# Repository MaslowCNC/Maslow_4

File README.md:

# Maslow Readme for machines version 4 and 4.1 Current through 2025
## Quicklinks:
Website where you can buy a kit and current assembly instrucitons:
<https://www.maslowcnc.com/>

📚 **Documentation Site (GitHub Pages):**
<https://maslowcnc.github.io/Maslow_4/>

📋 **Changelog (What's New):**
[CHANGELOG.md](./CHANGELOG.md) | [Release Notes v1.16](./docs/ReleaseNotes_v1.16.md) | [Release Notes v1.15](./docs/ReleaseNotes_v1.15.md)

Assembly instructions in wiki:
<https://github.com/MaslowCNC/Maslow_4/tree/assembling-the-arms-4-1>

Repository and wiki:
<https://github.com/MaslowCNC/Maslow_4/wiki>

Forums:
<https://forums.maslowcnc.com/>

How to edit this wiki:
<https://github.com/MaslowCNC/Maslow_4/blob/Maslow-Main/docs/HowToEditThisWiki.md>

This is a rough draft. For more info go to <https://www.maslowcnc.com>

# INTRO

## What is it? 
Maslow is a DIY 3 axis (x,y,z) computer numerical control (CNC) robot that controls a router to cut wood, plastic or other flat material.  It has been designed to work well on a 4x8 foot sheet of material or smaller and it is able to sculpt and cut vertically about 60 mm or 2.5 inches deep.  Maslow is designed around a small sled that carries the router and is anchored to an external frame by long belts that it uses to pull itself around.  This means that the core robot is very portable. It does require a stiff frame or anchors external to the robot.  It rides on top of the work being cut so it works well on cutting and sculpting shallow shapes but not giant bathtub sized hollows. Maslow is focused on accessiblility. 

Maslow's control software is a local website hosted inside the machine that you can access through USBC cable, Wifi direct to the machine, or through your local wifi network. It can be used with a phone or a computer. It recieves standard Gcode machine instruction files (.nc)  You will need cnc design software that can generate Gcode. There are many free or fancy options. 

The control software is built on top of FluidNC an open source cnc control software for ESP32 computers. Maslow4's pcb is an esp32 computer.

The FluidNC project wiki is here: 

<http://wiki.fluidnc.com/>

Github:

<https://github.com/bdring/FluidNC>

Donate to FluidNC:

Maslow4 is different from a gantry designed CNC router which are designed around a table that fits the material inside and then the robot moves forward and back on rails. It is much much less expensive than a gantry machine. It is in general less accurate than a good gantry machine. Gantry machines can also be 4 or 5 axis machines in which they can rotate the material in order to cut it at different angles. 

Maslow is a project developed by Barbour Smith and a community of volunteers and forum members as an open source project that is still under development.  It is portable, exciting, inexpensive and perhaps frustrating and still requires some troubleshooting and figuring out to get started.  Barbour has been working on iterations of this for more than a decade and many people have been successful at making many exciting projects including saunas, tables, signs, and a 30 foot catamaran! (link to project gallery) but it is not at the moment a perfect plug and play tool.  **If making your own portable blade wielding robot in an enthusiastic online community sounds fun, then you are probably in the right place.** 

# History (I don't know a lot here) 
 In ???? Barbour Smith designed the first Maslow as a wall mounted CNC routing robot that hung from two chains and pulled itself back and forth across a space. The robot at that point was designed around an Arduino Mega 2560 microcontroller and was an open source design. Barbour set up the forums and github groups and sold ??? machines. 

 It is still possible to make a Maslow Version 1, 2, or 3 and many people have been happy with them as useful tools. Makermade was a company that sold version ?2? under the open source license that is not affiliated directly with Maslow's developers. 

 The current version Maslow 4 was prototyped as 3D printed parts with standard hardware. It has four machine belts instead of two chains. The parts are not interchangable with earlier versions. It uses a custom printed circuit board PCB built around an ESP microcontroller. The board also incorporates motor controllers. 

It is still possible to 3D print your own parts and replacement parts. It is still possible to design and program your own generic ESP microcontroller and use off the shelf motor controllers. In ?2023? Barbour ran a successful Kickstarter campaign with which he used the proceeds to design and have injection molds made for injection molded parts and better compact custom PCBs. Injection molded parts are much stronger than most 3d printed parts. This is what you are buying when you buy a Maslow kit. The custom PCB, the custom wires, the motors and custom made hardware, nuts and bolts, and the injection molded plastics with fiberglass inclusions. 4.1 was the result of a second kickstarter campaign that upgraded the PCB, wire connectors, the nuts and bolts and other metal hardware as well as a better spool design.

# Community members who have made significant contributions:
bar founder and primary developer

dlang ?Programming?

Ian_ab?Programming? 

# How to get involved
Maslow is a truly open source project. The forums are active with helpers and anybody can add to the discussions there or add to the project here in the github repo.  You can't mess things up here as final commits have to be checked.
The creative community needs to share fun projects, fun adapatations of the robot and support frames, hacks and troubleshooting tips, programming fixes, and documentation. 

/Firmware is edited and developed by volunteers, you can try too, the Github Maslow AI can be asked to change the programming. 

Three D Printing files and parts lists will soon be in the repo for downloading and editing or adapting

/docs holds documentation and instructions.  If you have a good idea to make things more clear or help other people understand the machine you could add something there

To edit a file here navigate to the file you want to edit, open it, then click on the little pencil in the top corner and it will open an editing window. When you are editing you are making a temporary branch of the main repo. This branch is a copy of the main repo that can be compared and if useful written back into the main repo. The human readable document pages are written in markdown language, a kind of simple word processor. Markdown instructions are in a link at the bottom of the editing window.  Once you have edited the document you can commit changes and then make a pull request asking for it to be written back to the main branch.  

# Future of the project
Currently the focus is on making the Maslow4 run quickly and easily mostly through firmware development. Community members are playing with different 3d printed adaptations of the main parts as well as both larger and smaller frames. The goal would be to keep developing the software now and then have an updated hardware kit in several years. A sister project to Maslow is Abundance, which is working towards being an open source web browser based parametric cad system that could feed directly to Maslow <https://abundance.maslowcnc.com/>
(written 2025) 

# Safety and hazards
Power tools are inherently powerful and can be dangerous.  This is an open source project created and maintained by amatuer enthusiasts with designs that have not been tested or evaluated for safety. Follow any instructions here at your own risk and using your own judgement.  The authors of this project make no claims about the saftey or suitability of the designs, ideas, or instructions. Any safety advice is provided in good faith. Use and modify the information in this project at your own risk. 

Below is a list of common sense hazards for you to consider

## Hazards may include:
- **Electrical shock or fire** if used in a damp or wet area or if electrical insulation or protective covering is damaged or removed. Always check your wires, connections and PCB cover for damage. Make sure airflow to the machine is not blocked or restricted. Different routers and spindles will require different airflow. Do not leave the machine unattended while it is in use. Have a plan to cut power to the machine in an emergency. 
- **Dust inhalation and dust fire**. Routers create dust and heat as blades cut through material.  Evaluate the material you are cutting and take dust mitigation measures including working in the open air, using dust vacuum systems, dust masks and appropriate respirators.
- **Friction fire hazard.** Blades create heat through friction, this can cause material being cut or other nearby items to ignite, smoke, or smolder. This is especialy dangerous when a power tool gets stuck in one place or bound up in the material being cut. While the machine is running do not leave it unattended and test and evaluate the material being cut and the feed rate, moving speed, and rotational speed for suitablility for each job. Materials may produce fumes while being cut. 
- **Laceration, burns, pinching, and crushing**. Never touch the blade of a router without saftey measures. Router bits are very sharp and will be hot after use. The motors and belts can entangle hair or loose clothing and fingers or other body parts could be pinched or torn while the machine is moving. Care has been taken in the design to minimize these risks.  Keep clear of the the machine while motors are engaged. Make sure both the router and the control board are unplugged and off before changing bits or touching the machine.
- **Eye, skin, or equipment damage from backlash or flying debris**.  Spinning power tool blades can throw pieces of themselves or cut material at great speed. Robotic motors put belts and parts under strain which can result in breakage and pieces being thrown with speed. Wear eye protection at all times when the machine is running and only use the machine in a controlled environment where bystanders are protected from flying debris. Do not leave the machine unattended.
- **Hearing Damage**. Routers and robots can easily exceed safe noise thresholds while running. Wear appropriate hearing proection while the machine is in use.

## Overall saftey meaures
- Regularly check your machine  for evidence of wear or damage.
- Only use in a safe and controlled space. 
- Do not leave the machine running unattended.
- Use personal protective equipment including masks, respirators, gloves, hearing protection,  and eye protection. 
- Do not touch the machine while it is moving or turned on.
- Do not change blades while the machine is plugged in. 
- Have a fire suppression plan and equipment.
- Consider how you will cut power to the machine in an emergency.
- Check for loose parts, tools, keys, and if the blades are in an appropriate place before providing power to the machine. 
- Train yourself and anyone who will come in contact with the machine on your saftely plan. 

CNC routers are nice in that they may be operated at a greater distance than a handheld router.  Many of the vibration, inhalation, and flying debris dangers are less with a robotic controler.  CNC machines are dangerous when people leave them unattended and beacause there are more motors, more electrical connections, and more moving parts.

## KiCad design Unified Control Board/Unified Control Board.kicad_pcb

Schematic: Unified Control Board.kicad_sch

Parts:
C1, C7, C10, C18: 22uF; CAP-SMD_BD6.3-L6.6-W6.6-LS7.3-FD; MPN RT1J220M0607
C5, C9, C16, C160, C161, C162, C163: 100nF/100V; C0603; MPN CL10B104KC8NNNC
C8, C11, C19, C20, C26: 1uF; C0402; MPN CL05A105KA5NQNC
C21: 22uF; C0805; MPN CL21A226MAQNNNE
C22: 100nF; C0603; MPN CC0603KRX7R9BB104
C23: 10uF; C0805; MPN CL21A106KAYNNNE
C24, C25: 22pF; C0603; MPN CC0603JRNPO9BN220
C27, C74, C75: 330uF/50V; CAP-SMD_BD10.0-L10.3-W10.3-LS10.9-FD; MPN EEEFT1H331AP
C28: 220uF/50V; CAP-SMD_BD10.0-L10.3-W10.3-LS10.9-FD; MPN UCD1H221MNL1GS
C29: 12nF; C0402; MPN CC0402KRX7R9BB123; LCSC Part Name 1nF ±10% 50V X7R 0402 MLCC
C30: 82pF; C0402; MPN CC0402JRNPO9BN820; LCSC Part Name 1nF ±10% 50V X7R 0402 MLCC
C31: 100nF; C0603; MPN CC0603KRX7R9BB104; LCSC Part Name 1nF ±10% 50V X7R 0402 MLCC
C32: 10uF; C0805; MPN GRM21BR61H106KE43L; LCSC Part Name 10uF ±10% 50V
C33: 22uF; C0805; MPN CL21A226MAQNNNE; LCSC Part Name 10uF ±10% 50V
C34, C36, C42, C49, C54, C61: 100nF; C0603; MPN CC0603KRX7R9BB104; LCSC Part Name 100nF ±10% 50V
C39, C60: 100uF/50V; CAP-TH_BD8.0-P3.50-D0.6-FD; MPN 50YXF100MEFC8X11.5; LCSC Part Name 100uF ±20% 50V (alt: Chengx KM107M050F1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
C40, C44: 1uF; C0402; MPN CL05A105KA5NQNC; LCSC Part Name 1uF ±10% 25V
C56: 22uF; C0805; MPN CL21A226MAQNNNE; LCSC Part Name 22µF ±20% 16V X5R 0805 MLCC
C63: 22uF; C0805; MPN CL21A226MAQNNNE; LCSC Part Name 22uF ±20% 16V X5R 0805 MLCC
C72: 10uF/25V; C0805; MPN CL21A106KAYNNNE
C73: 220nF/100V; C0805; MPN CC0805KKX7R0BB224
CGQ1: IR12-21C/TR8; LED-SMD_IR12-21C-TR8; MPN IR12-21C/TR8; LCSC Part Name 65mA红外发射管
CN1, CN2, CN3, CN6: B02B-PASK(LF)(SN); CONN-TH_B02B-PASK; MPN B02B-PASK(LF)(SN)
CN4, CN5, CN7, CN8: B04B-PASK(LF)(SN); CONN-TH_B04B-PASK; MPN B04B-PASK(LF)(SN)
CN9, CN10, CN11: B3B-XH-2(LF)(SN); CONN-TH_B3B-XH-2-LF-SN; MPN B3B-XH-2(LF)(SN); LCSC Part Name 1x3P 间距:2.5mm 直插 系列:XH
D1, D2, D5: RB050L-60TE25; SMA_L4.2-W2.6-LS5.3-RD; MPN RB050L-60TE25
D3: SMCJ36A; SMC_L7.1-W6.2-LS8.1-R-RD; MPN SMCJ36A; LCSC Part Name SMCJ36A
D6: BZT52C15; D_SOD-123; MPN BZT52C15
H1, H2: SMTSOM330BTR; SMTSO-M3_SMD-Ring_Hole4.22; MPN SMTSOM330BTR
IR1: PT12-21C/TR8; SENSOR-SMD_L3.0-W2.0-RD; MPN PT12-21C/TR8; LCSC Part Name 940nm的NPN光电三极管
L1: 4.7uH; L_APV_ANR4030; MPN FNR4030S4R7MT
LED1: LED-0603_R; LED0603_RED; MPN KT-0603R
LED2: FC-DA1608BK-470H10; LED0603-RD; MPN NCD0603B1
LED3: green; LED0603-RD-YELLOW; MPN KT-0603YG; LCSC Part Name Green 570nm 0603 LED, Vf 2.0-2.2V, 30-4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
Q1: ME50P06-G; TO-252-2; MPN ME50P06-G
R1, R11, R12, R21: 680Ω; R0402; MPN 0402WGF6800TCE
R2, R3: 120Ω; R0603; MPN 0603WAF1200T5E
R4: 2.2kΩ; R0402; MPN 0402WGF2201TCE
R5, R7, R14, R15, R16, R17, R18, R22, R23, R24: 1kΩ; R0402; MPN 0402WGF1001TCE
R8, R13: 5.1kΩ; R0402; MPN 0402WGF5101TCE
R9, R10, R19, R20, R25, R26, R28: 10kΩ; R0402; MPN 0402WGF1002TCE
R27: 62kΩ; R0402; MPN 0402WGF6202TCE; LCSC Part Name 3.3kΩ ±1% 1/16W 0402 Chip Resistor
R29: 20kΩ; R0402; MPN 0402WGF2002TCE; LCSC Part Name 3.3kΩ ±1% 1/16W 0402 Chip Resistor
R30: 200kΩ; R0402; MPN 0402WGF2003TCE; LCSC Part Name 3.3kΩ ±1% 1/16W 0402 Chip Resistor
R31: 7.5kΩ; R0402; MPN 0402WGF7501TCE; LCSC Part Name 7.5kΩ ±1% 1/16W 0402 Chip Resistor
R38, R39, R45: 10kΩ; R0402; MPN 0402WGF1002TCE; LCSC Part Name 10kΩ ±1% 62.5mW 厚膜电阻
R44: 100Ω; R0402; MPN 0402WGF1000TCE; LCSC Part Name 100Ω ±1% 1/16W 0402 Chip Resistor
R58: 330Ω; R0402; MPN 0402WGF3300TCE; LCSC Part Name 330Ω ±1% 1/16W 0402 Chip Resistor
R59: 47kΩ; R0402; MPN 0402WGF4702TCE
R60: 100kΩ; R0402; MPN 0402WGF1003TCE
SW1, SW2, SW3: TSA002A3512A02; SW-SMD_BZCN_TSA002A35XXX; MPN TSA002A3512A02; LCSC Part Name 4.8*2*3.5mm 卧贴 轻触开关
U1: XT60PB-M.G.Y; CONN-TH_XT60PB-M; MPN XT60PB-M.G.Y
U2, U3, U4, U5: DRV8251ADDAR; SOIC-8-1EP_DDA0008B_ThermalVias_0.3mm; MPN DRV8251ADDAR
U6: TCA9546A; SOP-16_L5.0-W4.4-P0.65-LS6.4-BL; MPN TCA9546APWR,118
U7: ZDSD01GLGEAG; LGA-8_L6.0-W8.0-P1.27-BL; MPN ZDSD01GLGEAG
U8: ESP32-S3-WROOM-1; MPN ESP32-S3-WROOM-1
U9: TPS54360BDDAR; AP64350SP_SO-8-EP; MPN TPS54360BDDAR
USB1: KH-TYPE-C-16P; USB-C-SMD_KH-TYPE-C-16P; MPN KH-TYPE-C-16P

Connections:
3V3: C21.1, C22.2, C23.2, C33.1, C40.2, C42.2, C44.2, C49.2, C54.2, C56.1, C61.2, C63.2, CN4.4, CN5.4, CN7.4, CN8.4, L1.2, R5.2, R7.2, R14.2, R15.2, R16.2, R17.2, R18.2, R22.2, R23.1, R24.2, R25.2, R26.2, R27.1, R28.2, R38.2, R45.2, R58.2, SW3.2, U2.4 (VREF), U3.4 (VREF), U4.4 (VREF), U5.4 (VREF), U6.3 (/RESET), U6.16 (VDD), U7.8 (Vdd,power_supply), U8.2 (VDD33); also elsewhere on the board
/YLED: LED3.2 (A), R58.1
ADC BL: C20.2, R20.1, U8.12 (IO8)
ADC BR: C8.2, R9.1, U8.7 (IO7)
ADC TL: C19.2, R19.1, U8.11 (IO18)
ADC TR: C11.2, R10.1, U8.6 (IO6)
Axis Health LED: R3.2, U8.22 (IO14)
BEAMBREAK: IR1.1 (C), R45.1; also elsewhere on the board
BL IN1: U5.3 (IN1), U8.30 (IO37)
BL IN2: U5.2 (IN2), U8.29 (IO36)
BL OUT1: CN1.2, U5.6 (OUT1)
BL OUT2: CN1.1, U5.8 (OUT2)
BR IN1: U2.3 (IN1), U8.17 (IO9)
BR IN2: U2.2 (IN2), U8.15 (IO3)
BR OUT1: CN2.2, U2.6 (OUT1)
BR OUT2: CN2.1, U2.8 (OUT2)
BST: C31.1, U9.1 (BST)
BoardCOM1: U8.9 (IO16); also elsewhere on the board
BoardCOM2: U8.8 (IO15); also elsewhere on the board
BoardVersion: R4.2, R26.1, U8.10 (IO17)
Boot: SW1.1, U8.27 (IO0)
CLKV: U7.3 (CLK,clock_signal), U8.20 (IO12)
COMP: C30.1, R31.1, U9.6 (COMP)
COMP_Z: C29.1, R31.2
DETECTORLED: R44.2; also elsewhere on the board
FAULT: R28.1, U8.33 (IO40)
FB: R27.2, R29.1, U9.5 (FB)
GND: C1.2, C5.1, C7.2, C8.1, C9.1, C10.2, C11.1, C16.1, C18.2, C19.1, C20.1, C21.2, C22.1, C23.1, C24.1, C25.1, C26.1, C27.2, C28.2, C29.2, C30.2, C32.2, C33.2, C34.1, C36.1, C39.2, C40.1, C42.1, C44.1, C49.1, C54.1, C56.2, C60.2, C61.1, C63.1, C74.2, C75.2, C160.1, C161.1, C162.1, C163.1, CGQ1.1 (C), CN4.1, CN5.1, CN7.1, CN8.1, CN10.3, D3.1 (A), D5.2 (A), IR1.2 (E), LED1.2, LED2.1 (-), LED3.1 (C), R1.1, R4.1, R8.1, R11.1, R12.1, R13.1, R21.1, R29.2, R30.2, R39.2, R60.2, SW1.2, SW2.2, U1.2, U2.7 (GND), U2.9 (PAD), U3.7 (GND), U3.9 (PAD), U4.7 (GND), U4.9 (PAD), U5.7 (GND), U5.9 (PAD), U6.1 (A0), U6.2 (A1), U6.8 (VSS), U6.13 (A2), U7.4 (Vss,ground), U8.1 (GND), U8.40 (GND), U8.41 (EPAD), U9.7 (GND), U9.9 (EP), USB1.1 (EP), USB1.2 (EP), USB1.3 (EP), USB1.4 (EP), USB1.A1 (GND), USB1.A12 (GND), USB1.B1 (GND), USB1.B12 (GND); also elsewhere on the board
MCU_RST: C26.2, R25.1, U8.3 (EN)
MISOV: U7.6 (SD0,I/O_pin), U8.21 (IO13)
MOSIV: U7.5 (CMD,command_signal), U8.19 (IO11)
unnamed: CGQ1.2 (A), R44.1
unnamed: LED1.1, R3.1
unnamed: LED2.2 (+), R2.1
unnamed: R9.2, R11.2, U2.1 (IPROPI)
unnamed: R10.2, R12.2, U3.1 (IPROPI)
unnamed: R19.2, R21.2, U4.1 (IPROPI)
unnamed: R1.2, R20.2, U5.1 (IPROPI)
unnamed: R8.2, USB1.A5 (CC1)
unnamed: R13.2, USB1.B5 (CC2)
PHA1: CN9.1; also elsewhere on the board
PHA2: CN11.1; also elsewhere on the board
PHB1: CN9.2; also elsewhere on the board
PHB2: CN11.2; also elsewhere on the board
PHC1: CN9.3; also elsewhere on the board
PHC2: CN11.3; also elsewhere on the board
RT: R30.1, U9.4 (RT/CLK)
SCL: R14.1, U6.14 (SCL), U8.4 (IO4)
SCL0: CN7.2, R22.1, U6.5 (SC0)
SCL1: CN4.2, R23.2, U6.7 (SC1)
SCL2: CN8.2, R17.1, U6.10 (SC2)
SCL3: CN5.2, R15.1, U6.12 (SC3)
SDA: R7.1, U6.15 (SDA), U8.5 (IO5)
SDA0: CN7.3, R5.1, U6.4 (SD0)
SDA1: CN4.3, R24.1, U6.6 (SD1)
SDA2: CN8.3, R18.1, U6.9 (SD2)
SDA3: CN5.3, R16.1, U6.11 (SD3)
SD_CS: U7.2 (SD3,I/O_pin), U8.18 (IO10)
SPINDLE_BOOT0: C36.2, R39.1, SW3.1; also elsewhere on the board
SPINDLE_BOOT_X: U8.38 (IO2); also elsewhere on the board
SPINDLE_NRST: C34.2, R38.1, SW2.1; also elsewhere on the board
SPINDLE_RST_X: U8.39 (IO1); also elsewhere on the board
SS_GATE: C72.2, C73.1, D6.2 (A), Q1.1 (G), R59.2, R60.1
SW_NODE: C31.2, D5.1 (K), L1.1, U9.8 (SW)
TL IN1: U4.3 (IN1), U8.26 (IO45)
TL IN2: U4.2 (IN2), U8.23 (IO21)
TL OUT1: CN6.2, U4.6 (OUT1)
TL OUT2: CN6.1, U4.8 (OUT2)
TR IN1: U3.3 (IN1), U8.35 (IO42)
TR IN2: U3.2 (IN2), U8.34 (IO41)
TR OUT1: CN3.2, U3.6 (OUT1)
TR OUT2: CN3.1, U3.8 (OUT2)
USB5V: D2.2 (A), USB1.A4 (VBUS), USB1.A9 (VBUS), USB1.B4 (VBUS), USB1.B9 (VBUS)
USBD+: C24.2, U8.14 (IO20), USB1.A6 (DP1), USB1.B6 (DP2)
USBD-: C25.2, U8.13 (IO19), USB1.A7 (DN1), USB1.B7 (DN2)
VAC_CONTROL: CN10.1; also elsewhere on the board
VCC: C1.1, C5.2, C7.1, C9.2, C10.1, C16.2, C18.1, C27.1, C39.1, C60.1, C73.2, C74.1, C75.1, C160.2, C161.2, C162.2, C163.2, CN10.2, D1.2 (A), D3.2 (K), Q1.2 (D), U2.5 (VM), U3.5 (VM), U4.5 (VM), U5.5 (VM); also elsewhere on the board
VIN_RAW: C72.1, D6.1 (K), Q1.3 (S), R59.1, U1.1
VSUP: C28.1, C32.1, D1.1 (K), D2.1 (K), U9.2 (VIN)
WiFi LED: R2.2, U8.28 (IO35)

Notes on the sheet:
Motor Drivers
-PMOS gate VBUS pull-up to prevent reverse current to buck output -This provides low voltage drop BUCK starts at 3.3V default -Also prioritizes VBUS over BUCK
ESP32
3.3V Regulator
Beam Break Homing System
Microcontroller
BOOT button
ESP32-S3
Fan Control System
RESET button
Power Led
Integrated MOTOR Driver
200ma LDO / Power OR-ing with PMOS
Power Regulator
This is a low pass filter on the value from the current measuring parts
Type C - Female USB
Decoupling capacitors
Control for the vacuum dust collection system
USB
For Programming & Debugging
PHASE-CURRENT ADC (24V test of the 36V-branch front end) SOx (3.3k/3.3k bias, 1.65V = 0A) -> straight to ADS7038 AIN0-5; no ESP32 copy, no RC at the ADC pin. AIN0-2 = motor 1 A/B/C, AIN3-5 = motor 2 A/B/C, AIN6/AIN7 spare. Ref = AVDD = 3V3 (ratiometric with the bias). SPI on U10: IO37 CS (10k pull-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
M3 MOUNTING: SMD threaded standoffs soldered on the bottom under the two lower mounting holes (4.22 mm unplated hole, 6.6 mm ring, not connected). A bolt from the top threads straight in.

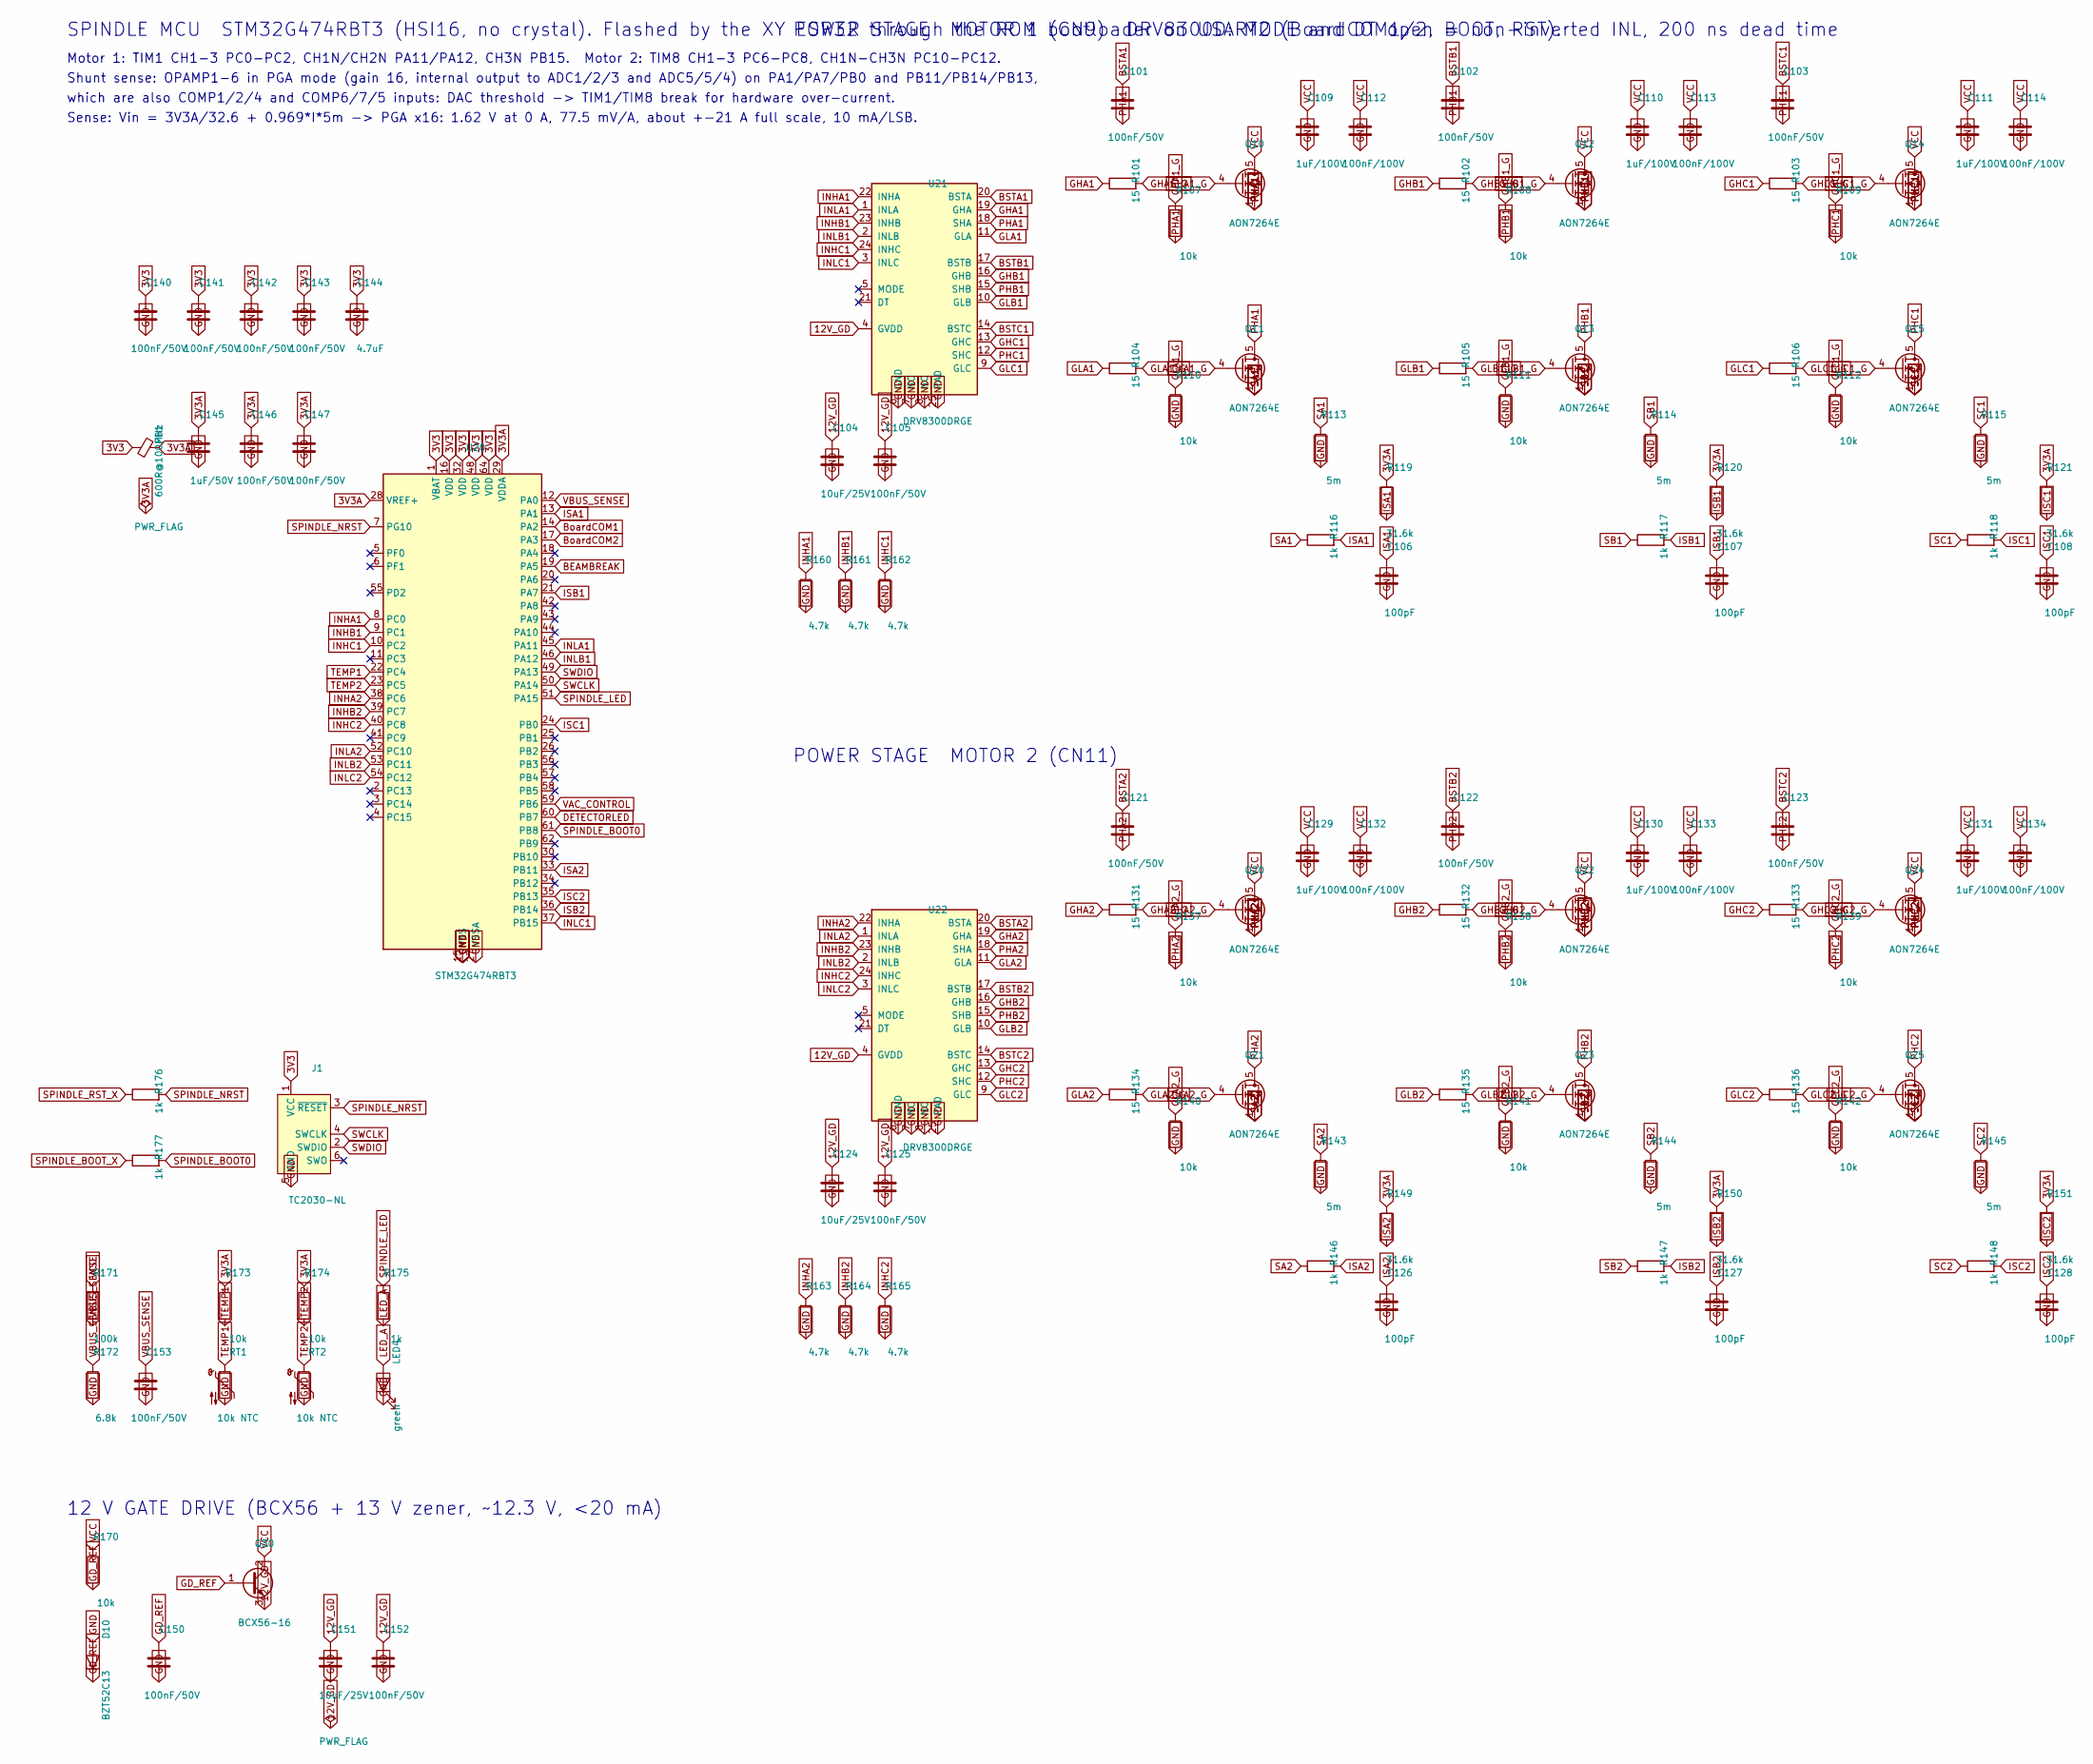
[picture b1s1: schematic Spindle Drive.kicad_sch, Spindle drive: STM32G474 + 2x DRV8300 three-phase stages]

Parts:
C101, C102, C103, C105, C121, C122, C123, C125, C140, C141, C142, C143, C146, C147, C150, C152, C153: 100nF/50V; C_0603_1608Metric; MPN CC0603KRX7R9BB104
C104, C124: 10uF/25V; C_0603_1608Metric; MPN GRM188R61E106MA73D
C106, C107, C108, C126, C127, C128: 100pF; C_0402_1005Metric; MPN 0402CG101J500NT
C109, C110, C111, C129, C130, C131: 1uF/100V; C_1206_3216Metric; MPN CL31B105KCHNNNE
C112, C113, C114, C132, C133, C134: 100nF/100V; C_0603_1608Metric; MPN CL10B104KC8NNNC
C144: 4.7uF; C_0603_1608Metric; MPN CL10A475KO8NNNC
C145: 1uF/50V; C_0603_1608Metric; MPN CL10A105KB8NNNC
C151: 10uF/25V; C_0805_2012Metric; MPN CL21A106KAYNNNE
D10: BZT52C13; D_SOD-123; MPN BZT52C13
FB1: 600R@100MHz; L_0603_1608Metric; MPN GZ1608D601TF
J1: TC2030-NL; Tag-Connect_TC2030-IDC-NL_2x03_P1.27mm_Vertical
LED4: green; LED_0603_1608Metric; MPN 19-213/Y2C-CQ2R2L/3T(CY)
Q10, Q11, Q12, Q13, Q14, Q15, Q20, Q21, Q22, Q23, Q24, Q25: AON7264E; AOS_DFN-8-1EP_3x3mm_P0.65mm; MPN AON7264E
Q30: BCX56-16; SOT-89-3; MPN BCX56-16
R101, R102, R103, R104, R105, R106, R131, R132, R133, R134, R135, R136: 15; R_0402_1005Metric; MPN 0402WGF150JTCE
R107, R108, R109, R110, R111, R112, R137, R138, R139, R140, R141, R142, R173, R174: 10k; R_0402_1005Metric; MPN 0402WGF1002TCE
R113, R114, R115, R143, R144, R145: 5m; R_1206_3216Metric; MPN STE1206M1W0R005FS
R116, R117, R118, R146, R147, R148, R175, R176, R177: 1k; R_0402_1005Metric; MPN 0402WGF1001TCE
R119, R120, R121, R149, R150, R151: 31.6k; R_0402_1005Metric; MPN 0402WGF3162TCE
R160, R161, R162, R163, R164, R165: 4.7k; R_0402_1005Metric; MPN 0402WGF4701TCE
R170: 10k; R_0603_1608Metric; MPN 0603WAF1002T5E
R171: 100k; R_0402_1005Metric; MPN 0402WGF1003TCE
R172: 6.8k; R_0402_1005Metric; MPN 0402WGF6801TCE
RT1, RT2: 10k NTC; R_0603_1608Metric; MPN NCP18XH103F03RB
U20: STM32G474RBT3; LQFP-64_10x10mm_P0.5mm; MPN STM32G474RBT3
U21, U22: DRV8300DRGE; VQFN-24-1EP_4x4mm_P0.5mm_EP2.45x2.45mm; MPN DRV8300DRGER

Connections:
3V3: C140.1, C141.1, C142.1, C143.1, C144.1, FB1.1, J1.1 (VCC), U20.1 (VBAT), U20.16 (VDD), U20.32 (VDD), U20.48 (VDD), U20.64 (VDD); also elsewhere on the board
3V3A: C145.1, C146.1, C147.1, FB1.2, R119.1, R120.1, R121.1, R149.1, R150.1, R151.1, R173.1, R174.1, U20.28 (VREF+), U20.29 (VDDA)
12V_GD: C104.1, C105.1, C124.1, C125.1, C151.1, C152.1, Q30.3 (E), U21.4 (GVDD), U22.4 (GVDD)
BEAMBREAK: U20.19 (PA5); also elsewhere on the board
BSTA1: C101.1, U21.20 (BSTA)
BSTA2: C121.1, U22.20 (BSTA)
BSTB1: C102.1, U21.17 (BSTB)
BSTB2: C122.1, U22.17 (BSTB)
BSTC1: C103.1, U21.14 (BSTC)
BSTC2: C123.1, U22.14 (BSTC)
BoardCOM1: U20.14 (PA2); also elsewhere on the board
BoardCOM2: U20.17 (PA3); also elsewhere on the board
DETECTORLED: U20.60 (PB7); also elsewhere on the board
GD_REF: C150.1, D10.1 (K), Q30.1 (B), R170.2
GHA1: R101.1, U21.19 (GHA)
GHA1_G: Q10.4 (G), R101.2, R107.1
GHA2: R131.1, U22.19 (GHA)
GHA2_G: Q20.4 (G), R131.2, R137.1
GHB1: R102.1, U21.16 (GHB)
GHB1_G: Q12.4 (G), R102.2, R108.1
GHB2: R132.1, U22.16 (GHB)
GHB2_G: Q22.4 (G), R132.2, R138.1
GHC1: R103.1, U21.13 (GHC)
GHC1_G: Q14.4 (G), R103.2, R109.1
GHC2: R133.1, U22.13 (GHC)
GHC2_G: Q24.4 (G), R133.2, R139.1
GLA1: R104.1, U21.11 (GLA)
GLA1_G: Q11.4 (G), R104.2, R110.1
GLA2: R134.1, U22.11 (GLA)
GLA2_G: Q21.4 (G), R134.2, R140.1
GLB1: R105.1, U21.10 (GLB)
GLB1_G: Q13.4 (G), R105.2, R111.1
GLB2: R135.1, U22.10 (GLB)
GLB2_G: Q23.4 (G), R135.2, R141.1
GLC1: R106.1, U21.9 (GLC)
GLC1_G: Q15.4 (G), R106.2, R112.1
GLC2: R136.1, U22.9 (GLC)
GLC2_G: Q25.4 (G), R136.2, R142.1
GND: C104.2, C105.2, C106.2, C107.2, C108.2, C109.2, C110.2, C111.2, C112.2, C113.2, C114.2, C124.2, C125.2, C126.2, C127.2, C128.2, C129.2, C130.2, C131.2, C132.2, C133.2, C134.2, C140.2, C141.2, C142.2, C143.2, C144.2, C145.2, C146.2, C147.2, C150.2, C151.2, C152.2, C153.2, D10.2 (A), J1.5 (GND), LED4.1 (K), R110.2, R111.2, R112.2, R113.2, R114.2, R115.2, R140.2, R141.2, R142.2, R143.2, R144.2, R145.2, R160.2, R161.2, R162.2, R163.2, R164.2, R165.2, R172.2, RT1.2, RT2.2, U20.15 (VSS), U20.27 (VSSA), U20.31 (VSS), U20.47 (VSS), U20.63 (VSS), U21.6 (GND), U21.7 (NC), U21.8 (NC), U21.25 (PAD), U22.6 (GND), U22.7 (NC), U22.8 (NC), U22.25 (PAD); also elsewhere on the board
INHA1: R160.1, U20.8 (PC0), U21.22 (INHA)
INHA2: R163.1, U20.38 (PC6), U22.22 (INHA)
INHB1: R161.1, U20.9 (PC1), U21.23 (INHB)
INHB2: R164.1, U20.39 (PC7), U22.23 (INHB)
INHC1: R162.1, U20.10 (PC2), U21.24 (INHC)
INHC2: R165.1, U20.40 (PC8), U22.24 (INHC)
INLA1: U20.45 (PA11), U21.1 (INLA)
INLA2: U20.52 (PC10), U22.1 (INLA)
INLB1: U20.46 (PA12), U21.2 (INLB)
INLB2: U20.53 (PC11), U22.2 (INLB)
INLC1: U20.37 (PB15), U21.3 (INLC)
INLC2: U20.54 (PC12), U22.3 (INLC)
ISA1: C106.1, R116.2, R119.2, U20.13 (PA1)
ISA2: C126.1, R146.2, R149.2, U20.33 (PB11)
ISB1: C107.1, R117.2, R120.2, U20.21 (PA7)
ISB2: C127.1, R147.2, R150.2, U20.36 (PB14)
ISC1: C108.1, R118.2, R121.2, U20.24 (PB0)
ISC2: C128.1, R148.2, R151.2, U20.35 (PB13)
LED_A: LED4.2 (A), R175.2
PHA1: C101.2, Q10.1 (S), Q10.2 (S), Q10.3 (S), Q11.5 (D), R107.2, U21.18 (SHA); also elsewhere on the board
PHA2: C121.2, Q20.1 (S), Q20.2 (S), Q20.3 (S), Q21.5 (D), R137.2, U22.18 (SHA); also elsewhere on the board
PHB1: C102.2, Q12.1 (S), Q12.2 (S), Q12.3 (S), Q13.5 (D), R108.2, U21.15 (SHB); also elsewhere on the board
PHB2: C122.2, Q22.1 (S), Q22.2 (S), Q22.3 (S), Q23.5 (D), R138.2, U22.15 (SHB); also elsewhere on the board
PHC1: C103.2, Q14.1 (S), Q14.2 (S), Q14.3 (S), Q15.5 (D), R109.2, U21.12 (SHC); also elsewhere on the board
PHC2: C123.2, Q24.1 (S), Q24.2 (S), Q24.3 (S), Q25.5 (D), R139.2, U22.12 (SHC); also elsewhere on the board
SA1: Q11.1 (S), Q11.2 (S), Q11.3 (S), R113.1, R116.1
SA2: Q21.1 (S), Q21.2 (S), Q21.3 (S), R143.1, R146.1
SB1: Q13.1 (S), Q13.2 (S), Q13.3 (S), R114.1, R117.1
SB2: Q23.1 (S), Q23.2 (S), Q23.3 (S), R144.1, R147.1
SC1: Q15.1 (S), Q15.2 (S), Q15.3 (S), R115.1, R118.1
SC2: Q25.1 (S), Q25.2 (S), Q25.3 (S), R145.1, R148.1
SPINDLE_BOOT0: R177.2, U20.61 (PB8); also elsewhere on the board
SPINDLE_BOOT_X: R177.1; also elsewhere on the board
SPINDLE_LED: R175.1, U20.51 (PA15)
SPINDLE_NRST: J1.3 (~RESET), R176.2, U20.7 (PG10); also elsewhere on the board
SPINDLE_RST_X: R176.1; also elsewhere on the board
SWCLK: J1.4 (SWCLK), U20.50 (PA14)
SWDIO: J1.2 (SWDIO), U20.49 (PA13)
TEMP1: R173.2, RT1.1, U20.22 (PC4)
TEMP2: R174.2, RT2.1, U20.23 (PC5)
VAC_CONTROL: U20.59 (PB6); also elsewhere on the board
VBUS_SENSE: C153.1, R171.2, R172.1, U20.12 (PA0)
VCC: C109.1, C110.1, C111.1, C112.1, C113.1, C114.1, C129.1, C130.1, C131.1, C132.1, C133.1, C134.1, Q10.5 (D), Q12.5 (D), Q14.5 (D), Q20.5 (D), Q22.5 (D), Q24.5 (D), Q30.2 (C), R170.1, R171.1; also elsewhere on the board

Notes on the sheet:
SPINDLE MCU STM32G474RBT3 (HSI16, no crystal). Flashed by the XY ESP32 through the ROM bootloader on USART2 (BoardCOM1/2, BOOT, RST).
Motor 1: TIM1 CH1-3 PC0-PC2, CH1N/CH2N PA11/PA12, CH3N PB15. Motor 2: TIM8 CH1-3 PC6-PC8, CH1N-CH3N PC10-PC12.
Shunt sense: OPAMP1-6 in PGA mode (gain 16, internal output to ADC1/2/3 and ADC5/5/4) on PA1/PA7/PB0 and PB11/PB14/PB13,
which are also COMP1/2/4 and COMP6/7/5 inputs: DAC threshold -> TIM1/TIM8 break for hardware over-current.
Sense: Vin = 3V3A/32.6 + 0.969*I*5m -> PGA x16: 1.62 V at 0 A, 77.5 mV/A, about +-21 A full scale, 10 mA/LSB.
12 V GATE DRIVE (BCX56 + 13 V zener, ~12.3 V, <20 mA)
POWER STAGE MOTOR 1 (CN9) DRV8300D: MODE and DT open = non-inverted INL, 200 ns dead time
POWER STAGE MOTOR 2 (CN11)

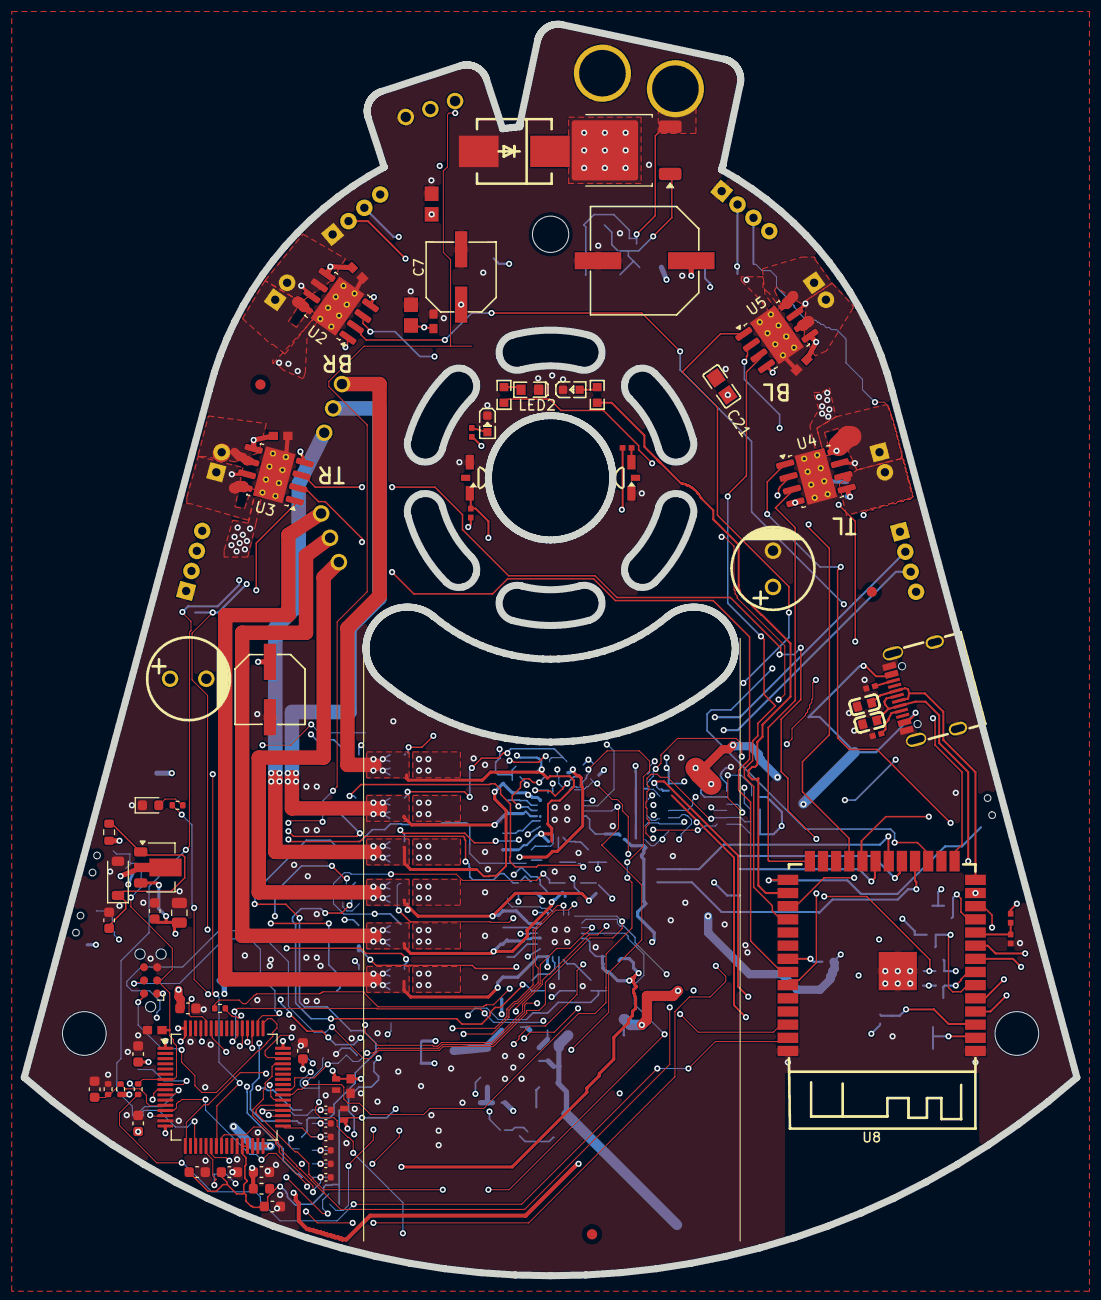
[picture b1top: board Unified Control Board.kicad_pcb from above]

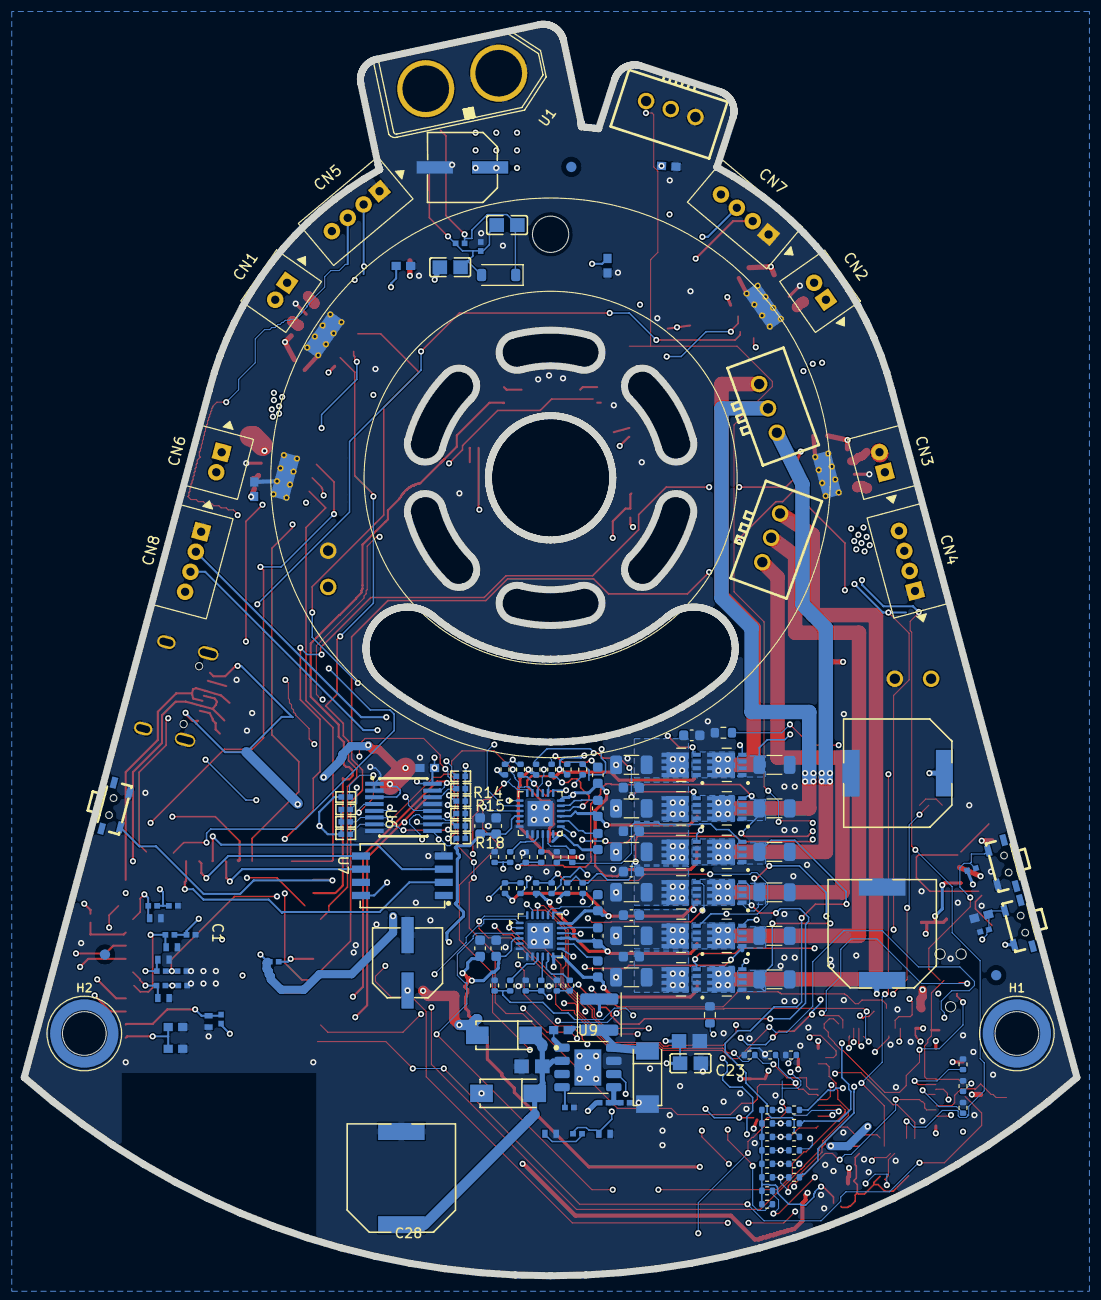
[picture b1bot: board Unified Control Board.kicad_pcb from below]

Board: 4 copper layers, 101.6 x 120.8 mm, 243 parts (170 on the bottom side), 144 nets.

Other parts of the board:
FID1, FID2, FID3, FID4, FID5, FID6: Fiducial; Fiducial_1mm_Mask2mm

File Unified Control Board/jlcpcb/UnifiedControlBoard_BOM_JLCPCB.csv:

"Comment","Designator","Footprint","LCSC Part #","Quantity"
"22uF","C1,C7,C10,C18","CAP-SMD_BD6.3-L6.6-W6.6-LS7.3-FD","C267472","4"
"100nF/100V","C5,C9,C16,C160,C161,C162,C163","C0603","C15725","7"
"1uF","C8,C11,C19,C20,C26,C40,C44","C0402","C52923","7"
"22uF","C21,C33,C56,C63","C0805","C45783","4"
"100nF","C22,C31,C34,C36,C42,C49,C54,C61","C0603","C14663","8"
"10uF","C23","C0805","C15850","1"
"22pF","C24,C25","C0603","C105620","2"
"330uF/50V","C27,C74,C75","CAP-SMD_BD10.0-L10.3-W10.3-LS10.9-FD","C178596","3"
"220uF/50V","C28","CAP-SMD_BD10.0-L10.3-W10.3-LS10.9-FD","C116211","1"
"12nF","C29","C0402","C576739","1"
"82pF","C30","C0402","C107011","1"
"10uF","C32","C0805","C440198","1"
"100uF/50V","C39,C60","CAP-TH_BD8.0-P3.50-D0.6-FD","C88728","2"
"10uF/25V","C72","C0805","C15850","1"
"220nF/100V","C73","C0805","C513710","1"
"100nF/50V","C101,C102,C103,C105,C121,C122,C123,C125,C140,C141,C142,C143,C146,C147,C150,C152,C153","C_0603_1608Metric","C14663","17"
"10uF/25V","C104,C124","C_0603_1608Metric","C91606","2"
"100pF","C106,C107,C108,C126,C127,C128","C_0402_1005Metric","C1546","6"
"1uF/100V","C109,C110,C111,C129,C130,C131","C_1206_3216Metric","C13832","6"
"100nF/100V","C112,C113,C114,C132,C133,C134","C_0603_1608Metric","C15725","6"
"4.7uF","C144","C_0603_1608Metric","C19666","1"
"1uF/50V","C145","C_0603_1608Metric","C15849","1"
"10uF/25V","C151","C_0805_2012Metric","C15850","1"
"IR12-21C/TR8","CGQ1","LED-SMD_IR12-21C-TR8","C53672","1"
"B02B-PASK(LF)(SN)","CN1,CN2,CN3,CN6","CONN-TH_B02B-PASK","C158050","4"
"B04B-PASK(LF)(SN)","CN4,CN5,CN7,CN8","CONN-TH_B04B-PASK","C265078","4"
"B3B-XH-2(LF)(SN)","CN9,CN10,CN11","CONN-TH_B3B-XH-2-LF-SN","C158003","3"
"RB050L-60TE25","D1,D2,D5","SMA_L4.2-W2.6-LS5.3-RD","C209642","3"
"SMCJ36A","D3","SMC_L7.1-W6.2-LS8.1-R-RD","C151282","1"
"BZT52C15","D6","D_SOD-123","C173427","1"
"BZT52C13","D10","D_SOD-123","C173428","1"
"600R@100MHz","FB1","L_0603_1608Metric","C1002","1"
"SMTSOM330BTR","H1,H2","SMTSO-M3_SMD-Ring_Hole4.22","C5221843","2"
"PT12-21C/TR8","IR1","SENSOR-SMD_L3.0-W2.0-RD","C53674","1"
"4.7uH","L1","L_APV_ANR4030","C167874","1"
"LED-0603_R","LED1","LED0603_RED","C2286","1"
"FC-DA1608BK-470H10","LED2","LED0603-RD","C84266","1"
"green","LED3","LED0603-RD-YELLOW","C2289","1"
"green","LED4","LED_0603_1608Metric","C2289","1"
"ME50P06-G","Q1","TO-252-2","C165230","1"
"AON7264E","Q10,Q11,Q12,Q13,Q14,Q15,Q20,Q21,Q22,Q23,Q24,Q25","AOS_DFN-8-1EP_3x3mm_P0.65mm","C431191","12"
"BCX56-16","Q30","SOT-89-3","C123402","1"
"680Ω","R1,R11,R12,R21","R0402","C25130","4"
"120Ω","R2,R3","R0603","C22787","2"
"2.2kΩ","R4","R0402","C25879","1"
"1kΩ","R5,R7,R14,R15,R16,R17,R18,R22,R23,R24","R0402","C11702","10"
"5.1kΩ","R8,R13","R0402","C25905","2"
"10kΩ","R9,R10,R19,R20,R25,R26,R28,R38,R39,R45","R0402","C25744","10"
"62kΩ","R27","R0402","C37825","1"
"20kΩ","R29","R0402","C25765","1"
"200kΩ","R30","R0402","C25764","1"
"7.5kΩ","R31","R0402","C25918","1"
"100Ω","R44","R0402","C25076","1"
"330Ω","R58","R0402","C25104","1"
"47kΩ","R59","R0402","C25792","1"
"100kΩ","R60","R0402","C25741","1"
"15","R101,R102,R103,R104,R105,R106,R131,R132,R133,R134,R135,R136","R_0402_1005Metric","C25083","12"
"10k","R107,R108,R109,R110,R111,R112,R137,R138,R139,R140,R141,R142,R173,R174","R_0402_1005Metric","C25744","14"
"5m","R113,R114,R115,R143,R144,R145","R_1206_3216Metric","C201272","6"
"1k","R116,R117,R118,R146,R147,R148,R175,R176,R177","R_0402_1005Metric","C11702","9"
"31.6k","R119,R120,R121,R149,R150,R151","R_0402_1005Metric","C11463","6"
"4.7k","R160,R161,R162,R163,R164,R165","R_0402_1005Metric","C25900","6"
"10k","R170","R_0603_1608Metric","C25804","1"
"100k","R171","R_0402_1005Metric","C25741","1"
"6.8k","R172","R_0402_1005Metric","C25917","1"
"10k NTC","RT1,RT2","R_0603_1608Metric","C13564","2"
"TSA002A3512A02","SW1,SW2,SW3","SW-SMD_BZCN_TSA002A35XXX","C2888932","3"
"XT60PB-M.G.Y","U1","CONN-TH_XT60PB-M","C19268037","1"
"DRV8251ADDAR","U2,U3,U4,U5","SOIC-8-1EP_DDA0008B_ThermalVias_0.3mm","C5218844","4"
"TCA9546A","U6","SOP-16_L5.0-W4.4-P0.65-LS6.4-BL","C201653","1"
"ZDSD01GLGEAG","U7","LGA-8_L6.0-W8.0-P1.27-BL","C2830323","1"
"ESP32-S3-WROOM-1","U8","ESP32-S3-WROOM-1","C2913204","1"
"TPS54360BDDAR","U9","AP64350SP_SO-8-EP","C524806","1"
"STM32G474RBT3","U20","LQFP-64_10x10mm_P0.5mm","C1235414","1"
"DRV8300DRGE","U21,U22","VQFN-24-1EP_4x4mm_P0.5mm_EP2.45x2.45mm","C3655801","2"
"KH-TYPE-C-16P","USB1","USB-C-SMD_KH-TYPE-C-16P","C709357","1"
